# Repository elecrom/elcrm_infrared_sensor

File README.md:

# elcrm_infrared_sensor

Containts schematic and layout files for infrared sensor

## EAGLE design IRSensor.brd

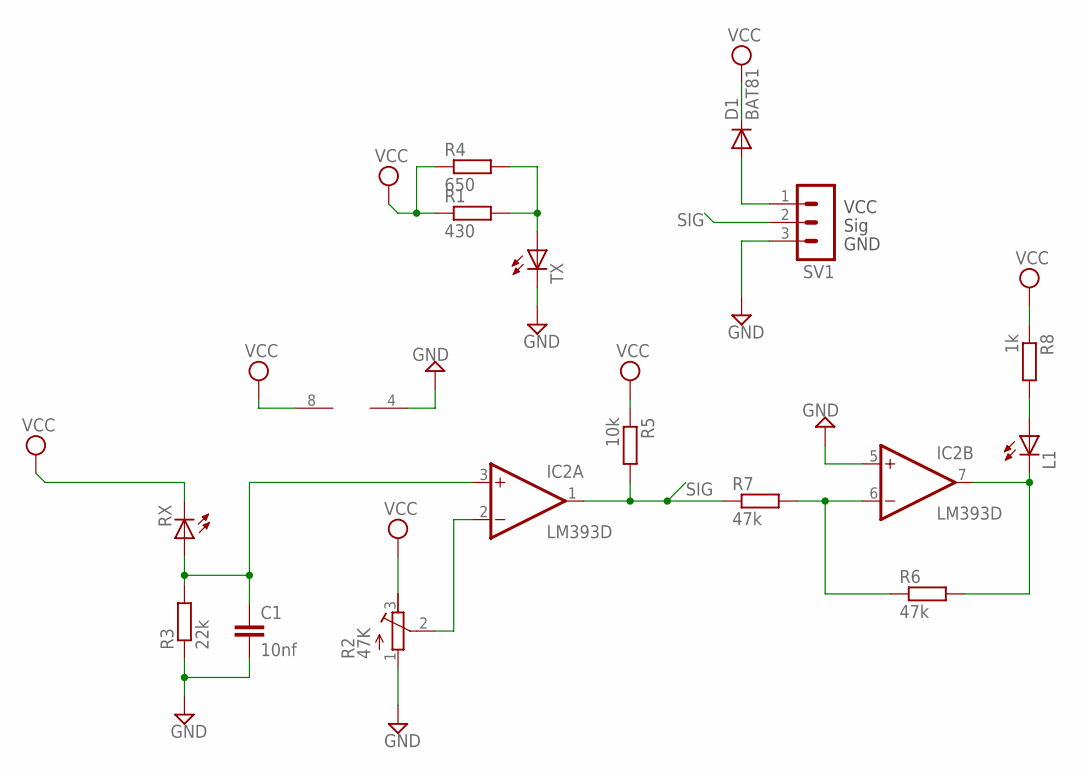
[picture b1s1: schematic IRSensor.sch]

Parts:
C1: 10nf; C1206
D1: BAT81; DO34-7
IC2: LM393D; SO08
L1: LEDCHIPLED_0805; CHIPLED_0805
R1: 430; 0204/7
R2: 47K; RTRIM64W
R3: 22k; M1206
R4: 650; 0204/7
R5: 10k; M1206
R6, R7: 47k; M1206
R8: 1k; M1206
RX: LED3MM
SV1: MA03-1
TX: LED3MM

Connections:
GND: C1.2, IC2.4 (V-), IC2.5 (+IN), R2.1 (E), R3.1, SV1.3, TX.K (C)
unnamed: R1.2, R4.2, TX.A
unnamed: D1.A, SV1.1
unnamed: L1.A, R8.2
unnamed: IC2.7 (OUT), L1.C, R6.2
unnamed: C1.1, IC2.3 (+IN), R3.2, RX.A
unnamed: IC2.6 (-IN), R6.1, R7.2
unnamed: IC2.2 (-IN), R2.2 (S)
SIG: IC2.1 (OUT), R5.2, R7.1, SV1.2
VCC: D1.C, IC2.8 (V+), R1.1, R2.3 (A), R4.1, R5.1, R8.1, RX.K (C)

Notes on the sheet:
GND
Sig
VCC

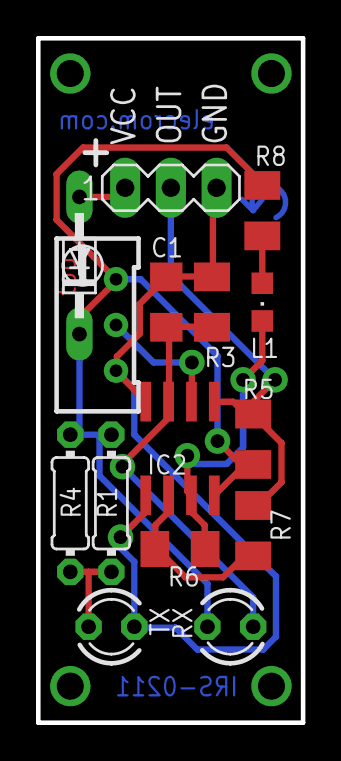
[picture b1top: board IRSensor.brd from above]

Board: 2 copper layers, 14.7 x 38.0 mm, 15 parts (0 on the bottom side), 10 nets.

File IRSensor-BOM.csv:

"Part";"Value";"Device";"Package";"Description";"";
"C1";"10nf";"C-EUC1206";"C1206";"CAPACITOR, European symbol";"";
"D1";"BAT81";"BAT81";"DO34-7";"DIODE";"";
"IC2";"LM393D";"LM393D";"SO08";"COMPARATOR";"";
"L1";"";"LEDCHIPLED_0805";"CHIPLED_0805";"LED";"";
"R1";"430";"R-EU_0204/7";"0204/7";"RESISTOR, European symbol";"";
"R2";"47K";"R-TRIMM64W";"RTRIM64W";"Trimm resistor";"";
"R3";"22k";"R-EU_M1206";"M1206";"RESISTOR, European symbol";"";
"R4";"650";"R-EU_0204/7";"0204/7";"RESISTOR, European symbol";"";
"R5";"10k";"R-EU_M1206";"M1206";"RESISTOR, European symbol";"";
"R6";"47k";"R-EU_M1206";"M1206";"RESISTOR, European symbol";"";
"R7";"47k";"R-EU_M1206";"M1206";"RESISTOR, European symbol";"";
"R8";"1k";"R-EU_M1206";"M1206";"RESISTOR, European symbol";"";
"RX";"";"LED3MM";"LED3MM";"LED";"";
"SV1";"";"MA03-1";"MA03-1";"PIN HEADER";"";
"TX";"";"LED3MM";"LED3MM";"LED";"";
